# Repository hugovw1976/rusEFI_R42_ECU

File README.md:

# rusEFI_R42_ECU

- 14x 4A low-side drivers
- 8x 5v ignition or general purpose outputs (or 4 igniters/ 4general purpose otputs)
- One H-bridge for electronic throttle
- 8x Analog voltage inputs
- 4x Analog temperature (5v pullup) inputs
- 2x VR crank/cam/vehicle speed inputs
- 6x hall cam/crank or digital input (-2 if VR sensors used)
- Base on proteus board (intended for use with proteus firmware microcontroller, pin matched to correspond output)

rusEFI project: https://github.com/rusefi/rusefi
Proteus project: https://github.com/mck1117/proteus

Please do not use the gerber files, the board is not tested yet!

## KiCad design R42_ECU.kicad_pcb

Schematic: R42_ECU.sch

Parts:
C1, C2, C3, C8, C9, C10, C11, C12, C13, C14, C15, C16, C25, C26, C27, C28, C31, C32, C33, C34, C39, C40, C48, C49, C54, C87: 10nF; 0603
C4, C5, C82, C83, C84, C85, C86, C97, C99, C104, C109, C111: 10nf; C0603
C6, C53, C59, C92, C95, C96: 1.0uF; 0603
C7, C17, C18, C21, C22, C23, C24, C50, C51, C55, C63, C64, C65, C66: 1nF; 0603
C19, C20, C29, C30, C35, C36, C37, C44, C45, C46, C47, C52, C57, C58, C60, C61, C62, C69, C70, C71, C72, C88, C115: 100nF; 0603
C38, C94: 4.7uF; 0603
C41, C91: 56uF; E3,5-8
C42, C67: 3.3nf; C0805
C43, C56, C68: 33nF; 0603
C73, C74: 680pf; C0603
C75, C76: 47PF; C0402
C77, C78: 330PF 50V; C0402
C79: 10nf; C0402
C80, C81: 10uf; C0805
C89: 270PF; 0603
C90, C93, C113: 10uf; C1206
C98: 22uf; 0603
C100, C101, C102, C103: 4.7uf; C0603
C105, C106: 2.2uf; C0603
C107, C108: 33pf; C0402
C110: 4.7uF; C0603
C112, C116: 1uf; C0603
C114: 100nf; 0603
D1: BLUE; LED-0603
D2, D5, D9, D15: SRV05-4.TCT; SOT95P280X145-6N
D3: SM15T33CA; DIOM7959X262N
D4, D11: PESD1CAN; SOT23
D6, D7: GREEN; LED-0603
D8: RED; LED-0603
D10: USBLC6-2SC6; SOT95P280X145-6N
D12, D13: C8678; SMA-DIODE
D14: Yellow; LED-0603
D16, D17, D18, D19, D20, D21: MBR0520LT1G; SOD-123FL
D22: MBR0520LT1G; SODFL3718X115
FB1: FERRITE_BEAD; BEADC2012X105N
J2: 47219-2001; MOLEX_47219-2001
J3: 62131021021
J4: CONN_06NO_SILK_NO_POP; 1X06_NO_SILK
J5: SJ1-3533NG; CUI_SJ1-3533NG
J6: 1734753-1; CONN_1734753-1
J7: CONN_02; 1X02
J8: CONN_06SILK_FEMALE_PTH; 1X06
J9: USB_CONN; 1X05_NO_SILK
L2: 10U; 0503
L3: 2.2U; L3225M
R1, R48, R49, R50, R76, R77: 10K; R0805
R2, R3, R4, R26, R27, R32, R44, R95: 2.2K; R0603
R5, R6, R7, R28, R29, R45: 3.3K; R0603
R8, R9, R10, R11, R12, R13, R14, R15: 100R; R0805
R16, R17, R34: 2.7K; R0603
R18, R19, R20, R21, R22, R40, R53, R54, R55, R56, R65, R66, R67, R78, R79, R88, R96, R97, R98, R101, R102: 10K; R0603
R23, R24, R25, R30, R31: 330R; R0402
R33, R46, R90: 12K; R0402
R35, R36, R37, R38, R57, R58, R59, R60, R68, R69, R70, R71: 5.6K; R0603
R39, R42, R43, R52, R72, R73, R74, R75: 470K; R0603
R41, R92: 120R; R0603
R47: B72530T6170K062; R-5
R51, R61, R62, R63, R100: 100K; R0402
R64, R81: 22K; R0402
R80: 2.7k; R0603
R82, R83: 33K; R0402
R84, R85, R86, R87: 1K; R0402
R89: 1R; R0603
R91: 68K; R0603
R93, R94: 470K; R0402
R99: 82k; R0603
R1020, R1021, R1022: 330R; R0805
R1023: 330r; R0805
RN1, RN2, RN3, RN4, RN5, RN6, RN7, RN8: 1K; 0603-ARC
RN11, RN13, RN14: 10K; 0603-ARC
S1, S3: JS202011SCQN; SW_JS202011SCQN
SW1, SW2: SPST_TACT-KMR2; KMR2
TP1, TP2, TP3: TEST-POINT3X5; PAD.03X.05
U1: HC-05; XCVR_HC-05
U2, U3, U5, U6, U7, U8: VNS3NV04DP-E; SOIC127P600X175-8N
U9: LPS25HBTR; PQFN60P250X250X80-10N
U10: TLE9201SG; SOP100P1030X260-13N
U11, U13, U14, U15: MIC4427YMM-TR; SOP65P490X110-8N
U12, U18, U31: 74HC2G17; SOP65P210X110-6N
U16: REF3033AIDBZR; SOT95P237X112-3N
U17, U22, U25, U28: MCP6004-E_SL; SOIC127P600X175-14N
U19: MAX9926UAEE+; SOP63P602X175-16N
U20: STMICROELECTRONICS_STM32F429ZGT6STMICROELECTRONIC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; STMICROELECTRONICS_STM32F429ZGT6_2
U21: TLE4251DATMA1; TO114P998X235-5
U23: LMR14020SDDAR; VREG_LM5017MR_NOPB
U24, U27: VD230; SO08
U26: VNLD5090TR-E; SOIC127P600X175-8N
U29: AMS1117-3.3; SOT229P700X180-4N
U32, U33, U34, U35: ISL9V3040D3STV; TO229P990X238-4N
U$1: MCP6002-E_SN; SOIC127P599X175-8N
U$3: 211PL562L0011
Y1: CRYSTAL_NX5032GA; CRYSTAL_2-SMD-5X3

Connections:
/3V3: C4.1, C5.1, C6.1, C19.1, C20.1, C38.2, C59.1, C61.1, C82.1, C83.1, C84.1, C85.1, C86.1, C97.1, C99.1, C100.1, C101.1, C102.1, C103.1, C115.2, C116.1, D6.A, FB1.2, J2.4 (VDD), J3.1, J4.1, J8.6, R1.2, R22.2, R32.1, R50.2, R64.2, R95.2, R96.1, R101.2, R102.2, SW2.1, SW2.3 (P1), TP2.P$1, U1.12 (3.3_VCC), U9.1 (VDD_IO), U9.6 (CS), U9.10 (VDD), U10.2 (VSO), U20.6 (VBAT), U20.17 (5_VDD), U20.30 (6_VDD), U20.39 (7_VDD), U20.52 (8_VDD), U20.62 (9_VDD), U20.72 (10_VDD), U20.84 (11_VDD), U20.95 (12_VDD), U20.108 (1_VDD), U20.121 (2_VDD), U20.131 (3_VDD), U20.143 (PDR_ON), U20.144 (4_VDD), U24.3 (VCC), U25.4 (VDD), U27.3 (VCC), U29.2 (VOUT), U29.4 (VOUT)
/5V: C29.1, C30.1, C35.1, C36.1, C43.1, C52.2, C53.1, C54.2, C56.1, C68.1, C89.2, C90.1, C93.1, D2.5, D5.5, D9.5, D15.5, D22.1 (C), L2.P$2 (2), R91.2, TP1.P$1, U11.6 (VS), U12.5 (VCC), U13.6 (VS), U14.6 (VS), U15.6 (VS), U16.1 (IN), U17.4 (VDD), U18.5 (VCC), U19.14 (VCC), U21.4 (ADJ), U22.4 (VDD), U28.4 (VDD), U29.3 (VIN), U31.5 (VCC), U$1.8 (VDD)
/5V_SENSORS: C37.1, C95.2, C98.2, R2.1, R3.1, R4.2, R16.2, R17.2, R26.1, R27.2, R34.2, R44.1, R80.2, U21.5 (Q), U$3.P53 (53)
/12V: C96.2, D3.1, D13.A, R47.1, R99.2, U21.1 (I), U21.2 (EN), U$3.P54 (54)
/12V_DIVIDED: C112.2, D15.1, R98.2, R99.1, U20.43 (PA7)
/12V_MR: C41.+, C113.1, D16.C, D17.C, D18.C, D19.C, D20.C, D21.C, U10.4 (VS), U$3.P15 (15)
/ANALOG1: R72.2, RN11.8 (2), U$3.P39 (39)
/ANALOG1_MCU: R21.2, R68.2, U20.26 (PC0)
/ANALOG2: R73.2, RN11.7 (2), U$3.P40 (40)
/ANALOG2_MCU: R20.2, R69.2, U20.27 (PC1)
/ANALOG3: R74.2, RN11.6 (2), U$3.P41 (41)
/ANALOG3_MCU: R19.2, R70.2, U20.28 (PC2)
/ANALOG4: R75.2, RN11.5 (2), U$3.P42 (42)
/ANALOG4_MCU: R18.2, R71.2, U20.29 (PC3)
/ANALOG5: R39.2, RN13.8 (2), U$3.P46 (46)
/ANALOG5_MCU: R35.2, R56.2, U20.34 (PA0-WKUP(PA0))
/ANALOG6: R42.2, RN13.7 (2), U$3.P45 (45)
/ANALOG6_MCU: R36.2, R55.2, U20.35 (PA1)
/ANALOG7: R43.2, RN13.6 (2), U$3.P44 (44)
/ANALOG7_MCU: R37.2, R54.2, U20.36 (PA2)
/ANALOG8: R52.2, RN13.5 (2), U$3.P43 (43)
/ANALOG8_MCU: R38.2, R53.2, U20.37 (PA3)
/ANALOG_T1: R17.1, RN14.5 (2), U$3.P48 (48)
/ANALOG_T1_MCU: R60.2, R65.2, U20.44 (PC4)
/ANALOG_T2: R16.1, RN14.6 (2), U$3.P37 (37)
/ANALOG_T2_MCU: R59.2, R67.2, U20.45 (PC5)
/ANALOG_T3: R80.1, RN14.7 (2), U$3.P47 (47)
/ANALOG_T3_MCU: R58.2, R78.2, U20.46 (PB0)
/ANALOG_T4: R34.1, RN14.8 (2), U$3.P38 (38)
/ANALOG_T4_MCU: R57.2, R79.2, U20.47 (PB1)
/AUX_SPI_CS: J8.5, U20.18 (PF6)
/AUX_SPI_MISO: J8.3, U20.20 (PF8)
/AUX_SPI_MOSI: J8.2, U20.21 (PF9)
/AUX_SPI_SCK: J8.4, U20.19 (PF7)
/BARO_SCL: R95.1, U9.2 (SCL/SPC), U20.69 (PB10)
/BARO_SDA: R32.2, U9.4 (SDA/SDI/SDO), U20.70 (PB11)
/CAM+: S3.2, S3.5, U$3.P50 (50)
/CAM+HALL: C23.2, R2.2, R7.1, S3.1, S3.4
/CAM+VR: R49.2, S3.3, S3.6
/CAM-: R48.2, U$3.P49 (49)
/CAM_IN: C24.2, R7.2, U18.3 (2A)
/CAM_VR_MCU: R50.1, U19.5 (COUT2), U20.59 (PE8)
/CAN1H: D4.2, R41.2, U27.7 (CANH), U$3.P30 (30)
/CAN1L: D4.1, R41.1, U27.6 (CANL), U$3.P29 (29)
/CAN1_RX: U20.114 (PD0), U27.4 (R)
/CAN1_TX: U20.115 (PD1), U27.1 (D)
/CAN2H: D11.2, R92.2, U24.7 (CANH), U$3.P55 (55)
/CAN2L: D11.1, R92.1, U24.6 (CANL), U$3.P56 (56)
/CAN2_RX: U20.73 (PB12), U24.4 (R)
/CAN2_TX: U20.74 (PB13), U24.1 (D)
/COIL1: C28.1, R11.2, U$3.P17 (17)
/COIL2: C27.1, R10.2, U$3.P16 (16)
/COIL3: C25.1, R8.2, U$3.P18 (18)
/COIL4: C26.1, R9.2, U$3.P19 (19)
/COIL5: C33.1, R14.2, U33.4 (EMITTER), U$3.P20 (20)
/COIL6: C34.1, R15.2, U32.4 (EMITTER), U$3.P9 (9)
/COIL7: C31.1, R12.2, U35.4 (EMITTER), U$3.P21 (21)
/COIL8: C32.1, R13.2, U34.4 (EMITTER), U$3.P8 (8)
/CRANK+: S1.2, S1.5, U$3.P35 (35)
/CRANK+HALL: C50.2, R44.2, R45.1, S1.1, S1.4
/CRANK+VR: R77.2, S1.3, S1.6
/CRANK-: R76.2, U$3.P36 (36)
/CRANK_IN: C51.2, R45.2, U18.1 (1A)
/CRANK_VR_MCU: R1.1, U19.4 (COUT1), U20.58 (PE7)
/D+: D10.1 (I/O1), D10.6 (I/O1), J6.3, J9.3, U20.104 (PA12)
/D-: D10.3 (I/O2), D10.4 (I/O2), J6.2, J9.2, U20.103 (PA11)
/DIR: U10.1 (DIR), U20.79 (PD10)
/DIS: R22.1, U10.11 (DIS), U20.80 (PD11)
/ETB_PWM: U10.12 (PWM), U20.81 (PD12)
/FILTERED1: C77.2, U20.14 (PF4), U25.6 (VINB-), U25.7 (VOUTB), U$1.2 (VINA-)
/FILTERED2: C78.1, U20.15 (PF5), U25.8 (VOUTC), U25.9 (VINC-), U$1.6 (VINB-)
/GND: C1.2, C2.2, C3.2, C4.2, C5.2, C6.2, C8.2, C9.2, C10.2, C11.2, C12.2, C13.2, C14.2, C15.2, C16.2, C17.1, C18.1, C19.2, C20.2, C21.1, C22.2, C23.1, C24.1, C25.2, C26.2, C27.2, C28.2, C29.2, C30.2, C31.2, C32.2, C33.2, C34.2, C35.2, C36.2, C37.2, C38.1, C39.1, C40.2, C41.-, C43.2, C44.2, C45.2, C46.2, C47.2, C48.1, C49.1, C50.1, C51.1, C52.1, C53.2, C54.1, C56.2, C57.2, C58.2, C59.2, C60.2, C61.2, C62.2, C63.1, C64.1, C65.1, C66.2, C68.2, C69.2, C70.2, C71.2, C72.2, C73.2, C74.1, C75.2, C76.1, C79.2, C82.2, C83.2, C84.2, C85.2, C86.2, C87.2, C90.2, C91.-, C92.2, C93.2, C94.2, C95.1, C96.1, C97.2, C98.1, C99.2, C100.2, C101.2, C102.2, C103.2, C104.1, C105.1, C106.1, C107.2, C108.2, C109.1, C110.1, C111.2, C112.1, C113.2, C114.2, C115.1, C116.2, D2.2, D3.2, D4.3, D5.2, D9.2, D10.2 (GND), D11.3, D12.A, D15.2, J2.6 (VSS), J2.G1 (GND@1), J2.G2 (GND@2), J2.G3 (GND@3), J2.G4 (GND@4), J3.3, J3.5, J3.9, J4.2, J5.1, J6.5, J8.1, J9.4, R18.1, R19.1, R20.1, R21.1, R23.2, R24.2, R25.2, R30.2, R31.2, R39.1, R40.1, R42.1, R43.1, R47.2, R52.1, R53.1, R54.1, R55.1, R56.1, R65.1, R66.1, R67.1, R72.1, R73.1, R74.1, R75.1, R78.1, R79.1, R81.1, R86.1, R87.1, R88.1, R90.2, R97.1, R98.1, R100.1, RN2.1, RN2.2 (1), RN2.3 (1), RN2.4 (1), RN4.1, RN4.2 (1), RN4.3 (1), RN4.4 (1), RN6.1, RN6.2 (1), RN6.3 (1), RN6.4 (1), RN7.1, RN7.2 (1), RN7.3 (1), RN7.4 (1), RN8.1, RN8.2 (1), RN8.3 (1), RN8.4 (1), SW1.2 (S), SW1.4 (S1), TP3.P$1, U1.13 (GND), U1.21 (GND), U1.22 (GND), U2.1 (SOURCE1), U2.3 (SOURCE2), U3.1 (SOURCE1), U3.3 (SOURCE2), U5.1 (SOURCE1), U5.3 (SOURCE2), U6.1 (SOURCE1), U6.3 (SOURCE2), U7.1 (SOURCE1), U7.3 (SOURCE2), U8.1 (SOURCE1), U8.3 (SOURCE2), U9.3 (RES), U9.5 (SDO/SA0), U9.8 (GND), U9.9 (GND), U10.6 (GND@1), U10.13 (GND@2), U11.3 (GND), U12.2 (GND), U13.3 (GND), U14.3 (GND), U15.3 (GND), U16.3 (GND), U17.11 (VSS), U18.2 (GND), U19.1 (INT_THRS1), U19.3 (BIAS1), U19.6 (BIAS2), U19.8 (INT_THRS2), U19.11 (GND), U19.13 (ZERO_EN), U20.16 (4_VSS), U20.31 (VSSA), U20.38 (5_VSS), U20.48 (PB2-BOOT1(PB2)), U20.51 (6_VSS), U20.61 (7_VSS), U20.83 (8_VSS), U20.94 (9_VSS), U20.107 (1_VSS), U20.120 (2_VSS), U20.130 (3_VSS), U21.3 (GND), U22.11 (VSS), U23.7 (GND), U23.9 (THERMALPAD), U24.2 (GND), U25.11 (VSS), U26.5 (SOURCE2), U26.7 (SOURCE1), U27.2 (GND), U28.11 (VSS), U29.1 (ADJ/GND), U31.2 (GND), U32.3 (COLLECTOR), U33.3 (COLLECTOR), U34.3 (COLLECTOR), U35.3 (COLLECTOR), U$1.4 (VSS), U$3.P10 (10), U$3.P31 (31), U$3.P32 (32)
/IGN1: RN7.7 (2), U13.4 (INB), U20.118 (PD4)
/IGN2: RN7.8 (2), U13.2 (INA), U20.117 (PD3)
/IGN3: RN7.6 (2), U11.2 (INA), U20.99 (PC9)
/IGN4: RN7.5 (2), U11.4 (INB), U20.98 (PC8)
/IGN5: RN8.8 (2), U15.2 (INA), U20.97 (PC7)
/IGN6: RN8.7 (2), U15.4 (INB), U20.93 (PG8)
/IGN7: RN8.6 (2), U14.2 (INA), U20.92 (PG7)
/IGN8: RN8.5 (2), U14.4 (INB), U20.91 (PG6)
/IN1: C65.2, R27.1, R29.1, U$3.P52 (52)
/IN1_IN: C66.1, R29.2, U31.1 (1A)
/IN1_MCU: U20.96 (PC6), U31.6 (1Y)
/IN2_MCU: U18.4 (2Y), U20.64 (PE11)
/IN3_MCU: U18.6 (1Y), U20.65 (PE12)
/IN4: C21.2, R4.1, R6.1, U$3.P33 (33)
/IN4_IN: C22.1, R6.2, U12.1 (1A)
/IN4_MCU: U12.6 (1Y), U20.67 (PE14)
/IN5: C17.2, R3.2, R5.1, U$3.P34 (34)
/IN5_IN: C18.2, R5.2, U12.3 (2A)
/IN5_MCU: U12.4 (2Y), U20.66 (PE13)
/IN6: C63.2, R26.2, R28.1, U$3.P51 (51)
/IN6_IN: C64.2, R28.2, U31.3 (2A)
/IN6_MCU: U20.68 (PE15), U31.4 (2Y)
/KNOCK1: C42.1, U$3.P12 (12)
/KNOCK2: C67.1, U$3.P11 (11)
/LED1: D8.A, U20.2 (PE3)
/LED2: D1.A, U20.3 (PE4)
/LED3: D7.A, U20.4 (PE5)
/LED4: D14.A, U20.5 (PE6)
/LS1: C48.2, D19.A, U26.8 (DRAIN1), U$3.P7 (7)
/LS1_MCU_: RN5.8 (2), RN6.5 (2), U20.123 (PD7)
/LS2: C49.2, D18.A, U26.6 (DRAIN2), U$3.P6 (6)
/LS2_MCU_: RN5.7 (2), RN6.6 (2), U20.124 (PG9)
/LS3: C11.1, D16.A, U5.7 (DRAIN1-1), U5.8 (DRAIN1), U$3.P22 (22)
/LS3_MCU_: RN5.6 (2), RN6.7 (2), U20.125 (PG10)
/LS4: C12.1, D17.A, U5.5 (DRAIN2-1), U5.6 (DRAIN2), U$3.P23 (23)
/LS4_MCU_: RN5.5 (2), RN6.8 (2), U20.126 (PG11)
/LS5: C10.1, D20.A, U6.7 (DRAIN1-1), U6.8 (DRAIN1), U$3.P5 (5)
/LS5_MCU_: RN1.8 (2), RN2.5 (2), U20.127 (PG12)
/LS6: C9.1, D21.A, U6.5 (DRAIN2-1), U6.6 (DRAIN2), U$3.P24 (24)
/LS6_MCU_: RN1.7 (2), RN2.6 (2), U20.128 (PG13)
/LS7: C2.1, U3.7 (DRAIN1-1), U3.8 (DRAIN1), U$3.P25 (25)
/LS7_MCU_: RN1.6 (2), RN2.7 (2), U20.129 (PG14)
/LS8: C1.1, U3.5 (DRAIN2-1), U3.6 (DRAIN2), U$3.P4 (4)
/LS8_MCU_: RN1.5 (2), RN2.8 (2), U20.134 (PB4(NJTRST))
/LS9: C3.1, U2.7 (DRAIN1-1), U2.8 (DRAIN1), U$3.P26 (26)
/LS10: C8.1, U2.5 (DRAIN2-1), U2.6 (DRAIN2), U$3.P3 (3)
/LS11: C15.1, U7.7 (DRAIN1-1), U7.8 (DRAIN1), U$3.P27 (27)
/LS11_MCU_: RN3.8 (2), RN4.5 (2), U20.137 (PB7)
/LS12: C16.1, U7.5 (DRAIN2-1), U7.6 (DRAIN2), U$3.P28 (28)
/LS12_MCU_: RN3.7 (2), RN4.6 (2), U20.139 (PB8)
/LS13: C14.1, U8.7 (DRAIN1-1), U8.8 (DRAIN1), U$3.P2 (2)
/LS13_MCU_: RN3.6 (2), RN4.7 (2), U20.140 (PB9)
/LS14: C13.1, U8.5 (DRAIN2-1), U8.6 (DRAIN2), U$3.P1 (1)
/LS14_MCU_: RN3.5 (2), RN4.8 (2), U20.141 (PE0)
/LS15_MCU: R84.2, R87.2, U20.142 (PE1)
/LS16_MCU: R85.2, R86.2, U20.1 (PE2)
/OUT+: C39.2, U10.5 (OUT1), U$3.P13 (13)
/OUT-: C40.1, U10.7 (OUT2), U$3.P14 (14)
/RESET: C111.1, J3.10, R96.2, SW1.1, SW1.3 (P1), U20.25 (NRST)
/SD_CS: J2.2 (CD/DAT3), U20.116 (PD2)
/SD_MISO: J2.7 (DAT0), U20.112 (PC11)
/SD_MOSI: J2.3 (CMD), U20.113 (PC12)
/SD_SCK: J2.5 (CLK), U20.111 (PC10)
/SHIELD: C114.1, J6.S1 (SHIELD), J6.S2 (SHIELD), J6.S3 (SHIELD), J9.5, R100.2
/SWCLK: J3.4, U20.109 (PA14(JTCK-SWCLK))
/SWDIO: J3.2, U20.105 (PA13(JTMS-SWDIO))
/UART_RX: J4.3, J7.2, U1.2 (UART-RX), U20.122 (PD6)
/UART_TX: J4.4, J7.1, U1.1 (UART-TX), U20.119 (PD5)
unnamed: C7.1, R77.1, U19.16 (IN1+)
unnamed: C7.2, R76.1, U19.15 (IN1-)
unnamed: C42.2, R51.1
unnamed: C44.1, D2.1, RN13.4 (1), U17.12 (VIND+)
unnamed: C45.1, D2.3, RN13.3 (1), U17.10 (VINC+)
unnamed: C46.1, D2.6, RN13.2 (1), U17.5 (VINB+)
unnamed: C47.1, D2.4, RN13.1, U17.3 (VINA+)
unnamed: C55.1, R49.1, U19.9 (IN2+)
unnamed: C55.2, R48.1, U19.10 (IN2-)
unnamed: C57.1, D5.1, RN14.4 (1), U28.12 (VIND+)
unnamed: C58.1, D5.3, RN14.3 (1), U28.10 (VINC+)
unnamed: C60.1, D5.6, RN14.2 (1), U28.5 (VINB+)
unnamed: C62.1, D5.4, RN14.1, U28.3 (VINA+)
unnamed: C67.2, R61.1
unnamed: C69.1, D9.1, RN11.4 (1), U22.12 (VIND+)
unnamed: C70.1, D9.3, RN11.3 (1), U22.10 (VINC+)
unnamed: C71.1, D9.6, RN11.2 (1), U22.5 (VINB+)
unnamed: C72.1, D9.4, RN11.1, U22.3 (VINA+)
unnamed: C73.1, R33.2, R62.1
unnamed: C74.2, R46.2, R63.1
unnamed: C75.1, R82.2, U25.5 (VINB+)
unnamed: C76.2, R83.2, U25.10 (VINC+)
unnamed: C77.1, R62.2, R82.1
unnamed: C78.2, R63.2, R83.1
unnamed: C79.1, R64.1, R81.2, U25.3 (VINA+), U25.12 (VIND+)
unnamed: C80.1, U$1.5 (VINB+), U$1.7 (VOUTB)
unnamed: C80.2, J5.3
unnamed: C81.1, U$1.1 (VOUTA), U$1.3 (VINA+)
unnamed: C81.2, J5.2
unnamed: C87.1, U23.6 (SS)
unnamed: C88.1, U23.1 (BOOT)
unnamed: C88.2, D12.C, L2.P$1 (1), U23.8 (SW)
unnamed: C89.1, R90.1, R91.1, U23.5 (FB)
unnamed: C91.+, C92.1, L3.2, U23.2 (VIN), U23.3 (EN)
unnamed: C94.1, R89.2
unnamed: C104.2, U16.2 (OUT), U20.32 (VREF+)
unnamed: C105.2, U20.71 (VCAP_1)
unnamed: C106.2, U20.106 (VCAP_2)
unnamed: C107.1, U20.24 (PH1-OSC_OUT(PH1)), Y1.1
unnamed: C108.1, U20.23 (PH0-OSC_IN(PH0)), Y1.2
unnamed: C109.2, C110.2, FB1.1, U20.33 (VDDA)
unnamed: D1.C, R25.1
unnamed: D6.C, R23.1
unnamed: D7.C, R30.1
unnamed: D8.C, R24.1
unnamed: D10.5 (VBUS), D22.2 (A), J6.1, J9.1
unnamed: D13.C, L3.1, R89.1
unnamed: D14.C, R31.1
unnamed: R8.1, U11.7 (OUTA)
unnamed: R9.1, U11.5 (OUTB)
unnamed: R10.1, U13.7 (OUTA)
unnamed: R11.1, U13.5 (OUTB)
unnamed: R33.1, R93.2, U25.1 (VOUTA)
unnamed: R35.1, U17.1 (VOUTA), U17.2 (VINA-)
unnamed: R36.1, U17.6 (VINB-), U17.7 (VOUTB)
unnamed: R37.1, U17.8 (VOUTC), U17.9 (VINC-)
unnamed: R38.1, U17.13 (VIND-), U17.14 (VOUTD)
unnamed: R40.2, U27.8 (RS)
unnamed: R46.1, R94.2, U25.14 (VOUTD)
unnamed: R51.2, R93.1, U25.2 (VINA-)
unnamed: R57.1, U28.1 (VOUTA), U28.2 (VINA-)
unnamed: R58.1, U28.6 (VINB-), U28.7 (VOUTB)
unnamed: R59.1, U28.8 (VOUTC), U28.9 (VINC-)
unnamed: R60.1, U28.13 (VIND-), U28.14 (VOUTD)
unnamed: R61.2, R94.1, U25.13 (VIND-)
unnamed: R66.2, U24.8 (RS)
unnamed: R68.1, U22.1 (VOUTA), U22.2 (VINA-)
unnamed: R69.1, U22.6 (VINB-), U22.7 (VOUTB)
unnamed: R70.1, U22.8 (VOUTC), U22.9 (VINC-)
unnamed: R71.1, U22.13 (VIND-), U22.14 (VOUTD)
unnamed: R84.1, U26.3 (IN2)
unnamed: R85.1, U26.1 (IN1)
unnamed: R88.2, U23.4 (RT/SYNC)
unnamed: R97.2, SW2.2 (S), SW2.4 (S1), U20.138 (BOOT0)
unnamed: R101.1, U20.8 (PC14-OSC32_IN(PC14))
unnamed: R102.1, U20.9 (PC15-OSC32_OUT(PC15))
unnamed: R1020.1, U32.1 (GATE)
unnamed: R15.1, R1020.2, U15.5 (OUTB)
unnamed: R14.1, R1021.1, U15.7 (OUTA)
unnamed: R1021.2, U33.1 (GATE)
unnamed: R1022.1, U34.1 (GATE)
unnamed: R13.1, R1022.2, U14.5 (OUTB)
unnamed: R1023.1, U35.1 (GATE)
unnamed: R12.1, R1023.2, U14.7 (OUTA)
unnamed: RN1.1, U2.4 (INPUT2)
unnamed: RN1.2 (1), U2.2 (INPUT1)
unnamed: RN1.3 (1), U3.4 (INPUT2)
unnamed: RN1.4 (1), U3.2 (INPUT1)
unnamed: RN3.1, U6.4 (INPUT2)
unnamed: RN3.2 (1), U6.2 (INPUT1)
unnamed: RN3.3 (1), U5.4 (INPUT2)
unnamed: RN3.4 (1), U5.2 (INPUT1)
unnamed: RN5.1, U8.4 (INPUT2)
unnamed: RN5.2 (1), U8.2 (INPUT1)
unnamed: RN5.3 (1), U7.4 (INPUT2)
unnamed: RN5.4 (1), U7.2 (INPUT1)
unnamed: U11.1 (NC), U11.8 (NC)
unnamed: U13.1 (NC), U13.8 (NC)
unnamed: U14.1 (NC), U14.8 (NC)
unnamed: U15.1 (NC), U15.8 (NC)

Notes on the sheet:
CRANK SENSOR
COIL DRIVERS
POWER
LS DRIVERS/GPO
ANALOG INPUT
CANBUS
5V SENSOR
HALL SENSORS
EXTENCIONS
BLUETOOTH
BARO SENSOR
CONNECTORS
SEL_SWITCH
ETB
KNOCK
MICRO SD
USB
MCU

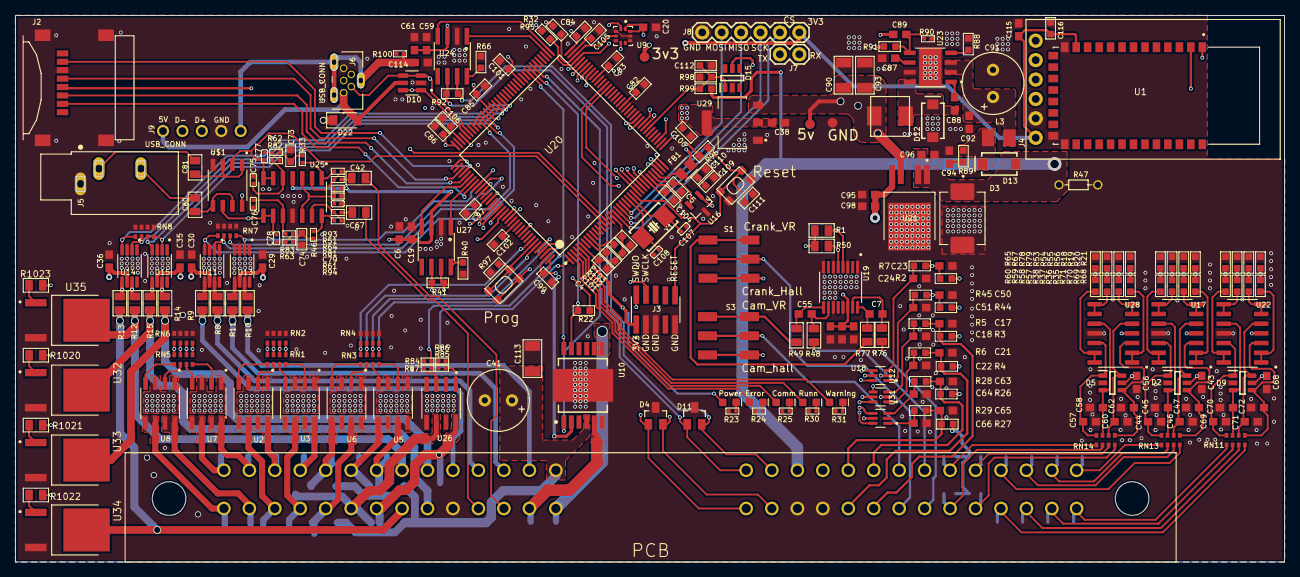
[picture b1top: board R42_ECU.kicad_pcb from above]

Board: 4 copper layers, 166.0 x 71.5 mm, 309 parts (0 on the bottom side), 240 nets.

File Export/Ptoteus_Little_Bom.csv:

Qty,Value,Device,Package,LCSC PART #,MOUSER PART #,Parts
1,B72530T6170K062,VARISTOR-5,R-5,,652-MOV-07D220K,R47
5,100K,SMD-RES-100K-1%-1/16W(0402),R0402,C25741,,"R51, R61, R62, R63, R100"
8,100R,SMD-RES-100R-5%-1/8W(0805),R0805,C441975,,"R8, R9, R10, R11, R12, R13, R14, R15"
3,10K,4R-N0603-ARC,0603-ARC,C29718,,"RN11, RN13, RN14"
21,10K,SMD-RES-10K-1%-1/10W(0603),R0603,C25804,,"R18, R19, R20, R21, R22, R40, R53, R54, R55, R56, R65, R66, R67, R78, R79, R88, R96, R97, R98, R101, R102"
6,10K,SMD-RES-10K-1%-1/4W(0805),R0805,C161788,,"R1, R48, R49, R50, R76, R77"
2,120R,SMD-RES-120R-5%-1/10W(0603),R0603,C22787,,"R41, R92"
8,1K,4R-N0603-ARC,0603-ARC,C20197,,"RN1, RN2, RN3, RN4, RN5, RN6, RN7, RN8"
4,1K,SMD-RES-1K-1%-1/16W(0402),R0402,C11702,,"R84, R85, R86, R87"
1,1R,SMD-RES-1R-5%-1/10W(0603),R0603,C22936,,R89
8,2.2K,SMD-RES-2.2K-5%-1/10W(0603),R0603,C4190,,"R2, R3, R4, R26, R27, R32, R44, R95"
4,2.7K,SMD-RES-2.7K-1%-1/10W(0603),R0603,C328353,,"R16, R17, R34, R80"
2,22K,SMD-RES-22R-1%-1/16W(0402),R0402,C25768,,"R64, R81"
6,3.3K,SMD-RES-3.3K-1%-1/10W(0603),R0603,C22978,,"R5, R6, R7, R28, R29, R45"
5,330R,SMD-RES-330R-1%-1/16W(0402),R0402,C25104,,"R23, R24, R25, R30, R31"
4,330R,SMD-RES-330R-1%-1/8W(0805),R0805,C441945,,"R1020, R1021, R1022, R1023"
2,33K,SMD-RES-33K-1%-1/16W(0402),R0402,C25779,,"R82, R83"
8,470K,SMD-RES-470K-1%-1/10W(0603),R0603,C23178,,"R39, R42, R43, R52, R72, R73, R74, R75"
2,470K,SMD-RES-470K-1%-1/16W(0402),R0402,C25790,,"R93, R94"
12,5.6K,SMD-RES-5.6K-1%-1/10W(0603),R0603,C114627,,"R35, R36, R37, R38, R57, R58, R59, R60, R68, R69, R70, R71"
1,68K,SMD-RES-68K-1%-1/10W(0603),R0603,C23231,,R91
1,82k,SMD-RES-82K-1%-1/10W(0603),R0603,C23254,,R99
8,1.0uF,1uF ±10% 50V X7R 0603,C0603,C525334,,"C6, C53, C59, C92, C95, C96, C112, C116"
24,100nF,100nF ±10% 50V X7R 0603,C0603,C14663,,"C19, C20, C29, C30, C35, C36, C37, C44, C45, C46, C47, C52,  C57, C58, C60, C61, C62, C69, C70, C71, C72, C88, C114, C115"
38,10nF,10nF ±10% 50V X7R 0603,C0603,C57112,,"C1, C2, C3, C4, C5 C8, C9, C10, C11, C12, C13, C14, C15, C16, C25, C26, C27, C28, C31, C32, C33, C34, C39, C40, C48, C49, C54, C82, C83, C84, C85, C86,C87, C97, C99, C104, C109, C111"
1,10nf,CERAMIC-10NF-50V-10%-X7R(0402),C0402,C15195,,C79
2,10uf,10uF ±10% 16V X7R 0805,C0805,C95841,,"C80, C81"
3,10uf,10uF ±10% 25V X7R 1206,C1206,C14860,,"C90, C93, C113"
14,1nF,1nF ±10% 50V X7R 0603,C0603,C1588,,"C7, C17, C18, C21, C22, C23, C24, C50, C51, C55, C63, C64, C65, C66"
2,2.2uf,2.2uF ±10% 25V X7R 0603,C0603,C99228,,"C105, C106"
1,22uf,22uF ±20% 10V X5R 0603,C0603,C84419,,C98
1,270PF,270pF ±10% 50V X7R 0603,C0603,C1608,,C89
2,3.3nf,3.3nF ±10% 50V X7R 0805,C0805,C53175,,"C42, C67"
2,330PF 50V,330pF ±10% 50V X7R 0402,C0402,C1535,,"C77, C78"
3,33nF,33nF ±10% 50V X7R 0603,C0603,C21117,,"C43, C56, C68"
2,33pf,33pF ±5% 50V C0G 0402,C0402,C1562,,"C107, C108"
7,4.7uF,4.7uF ±10% 35V X5R 0603,C0603,C329940,,"C38, C94, C100, C101, C102, C103, C110"
2,47PF,47pF ±5% 50V C0G 0402,C0402,C1567,,"C75, C76"
2,680pf,680pF ±10% 50V X7R 0603,C0603,C1630,,"C73, C74"
2,56uF,CPOL-USE3.5-8,"E3,5-8",,667-EEH-AZF1H560,"C41, C91"
1,10U,"10uH ±20% 3.2A 125mΩ SMD,5.2x5.4x3.0mm",0503,C139506,,L2
1,2.2U,2.2uH ±5% 320mA 1Ω 1210 Inductors,1210,C36828,,L3
3,74HC2G17,Dual non-inverting Schmitt trigger,SOT-363_SC-70-6,C94189,,"U12, U18, U31"
1,AMS1117-3.3,AMS1117-3.3,SOT-223,C6186,,U29
2,SMA_DIODE,Schottky Barrier Diodes 40V 3A 500mV @ 3A,SMA(DO-214AC),C85098,,"D12, D13"
6,DSS34,DIODE_SOD-123FL,SOD-123FL,C511866,,"D16, D17, D18, D19, D20, D21"
1,B5819W,Schottky Barrier Diodes,SOD-123FL,C8598,,D22
2,PESD1CAN,PESD1CAN,SOT23,C343993,,"D4, D11"
1,SM15T33CA,BIDIRECTIONAL TVS,SMC(DO-214AB),C133707,,D3
4,SRV05-4.TCT,SRV05-4.TCT,SOT-23-6,C85364,,"D2, D5, D9, D15"
1,USBLC6-2SC6,SOT-23-6 Diodes,SOT-23-6,C7519,,D10
1,Yellow,LED-YELLOW0603,LED-0603,C84268,,D14
1,Blue,LED-BLUE0603,LED-0603,C72041,,D1
1,Red,LED-RED0603,LED-0603,C72044,,D8
2,Green,LED-GREEN0603,LED-0603,C72043,,"D6, D7"
2,K3-2235S-F1,DPDT On-On SMD Toggle Switches,SW_JS202011SCQN,C223858,,"S1, S3"
2,KMR221GLFS,SPST_SMD Tactile Switches,SMD 4.6x2.8,C72443,,"SW1, SW2"
4,ISL9V3040D3ST,Ignition IGBT,TO-252AA,C462128,512-ISL9V3040D3ST,"U32, U33, U34, U35"
1,LMR14020SDDAR,40V 2A DC-DC Converters,SO PowerPAD-8,C187824,,U23
1,LPS25HBTR,Pressure Sensors,HLGA-10L,C87898,,U9
1,MAX9926UAEE/V+,Sensor Interface ICs,QSOP-16,C2678421,700-MAX9926UAEE/V+,U19
1,MCP6002T-E/MS,Low Power OpAmps,SOIC-8_150mil,C7377,,U$1
4,MCP6004T,Low Power OpAmps,SOIC-14,C7378,579-MCP6004T-I/ST,"U17, U22, U25, U28"
4,MIC4427YMM-TR,MIC4427YMM-TR,MSOP-8,C144222,998-MIC4427YMMTR,"U11, U13, U14, U15"
1,REF3033AIDBZR,Voltage References,SOT-23(SOT-23-3),C36658,,U16
1,STMICROELECTRONICS,STM32F429ZGT6,LQFP-144_20x20x05P,C46525,,U20
1,TLE4251DATMA1,LDO Voltage Regulators,TO252-5,C539669,726-TLE4251DATMA1,U21
1,IFX9201SGAUMA1,6 A H-Bridge with SPI,SO-12,C112633,,U10
2,SN65HVD230DR,Transceiver CAN 1/1 1Mbps,SOIC-8_150mil,C12084,,"U24, U27"
1,VNLD5090TR-E,MOSFET Gate Drivers,SO-8,C222209,511-VNLD5090TR-E,U26
6,VNS3NV04PTR-E,MOSFET Gate Drivers,SO-8,C146561,511-VNS3NV04PTR-E,"U2, U3, U5, U6, U7, U8"
1,8MHz ±10ppm 20pF 60Ω,SMD Crystal Resonators,SMD-5032_2P,C115962,,Y1
1,FERRITE_BEAD,Ferrite Beads,F0805,C1015,,FB1
1,USB_CONN,TE ,1734753-1,C305989,571-1734753-1,J6

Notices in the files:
parts and their libraries:
SparkFun-DiscreteSemi: Licensing: Creative Commons ShareAlike 4.0 International - https://creativecommons.org/licenses/by-sa/4.0
